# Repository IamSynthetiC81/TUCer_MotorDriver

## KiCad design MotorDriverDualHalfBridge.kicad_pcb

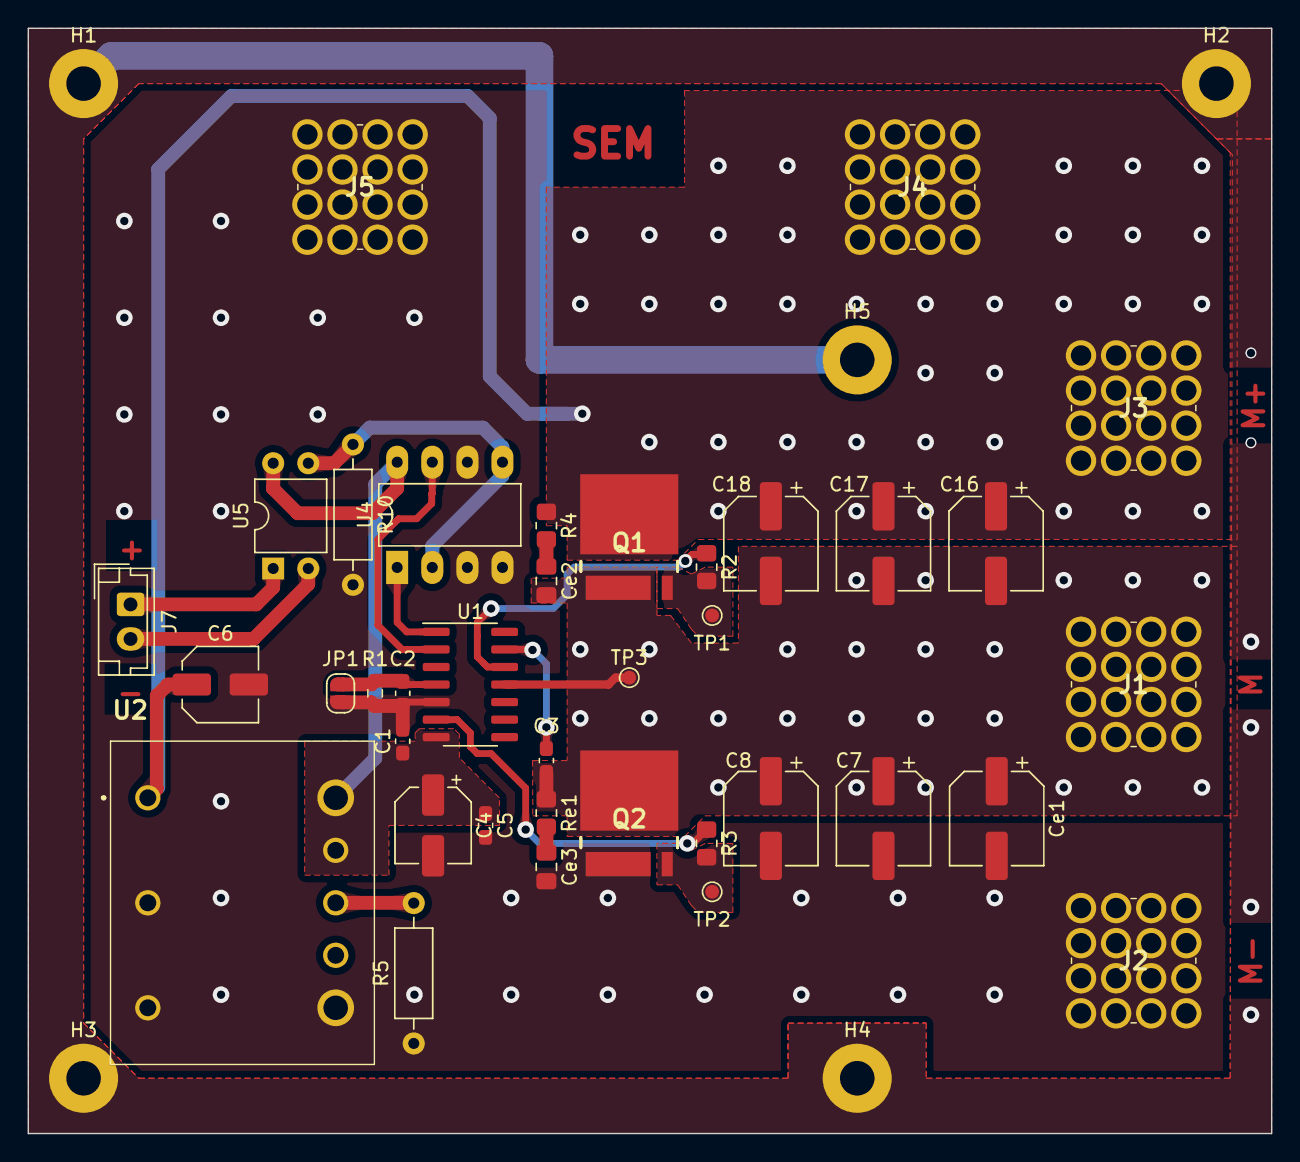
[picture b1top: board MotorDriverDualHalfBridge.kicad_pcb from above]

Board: 2 copper layers, 90.0 x 80.0 mm, 42 parts (0 on the bottom side), 19 nets.

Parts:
C1: 1uF; C_0603_1608Metric_Pad1.08x0.95mm_HandSolder
C2: 1nF; C_0603_1608Metric_Pad1.08x0.95mm_HandSolder
C3: 4.7uF; C_0603_1608Metric_Pad1.08x0.95mm_HandSolder
C4: 22uF; CP_Elec_5x5.8
C5: 0.1uF; C_0603_1608Metric_Pad1.08x0.95mm_HandSolder
C6: 100uF; C_Elec_5x5.8
C7, C8, C16, C17, C18: 100nF; CP_Elec_6.3x5.4_Nichicon
Ce1: 100nF; CP_Elec_6.3x5.4_Nichicon
Ce2: C_{SNUBH}; C_0805_2012Metric_Pad1.18x1.45mm_HandSolder
Ce3: C_{SNUBL}; C_0805_2012Metric_Pad1.18x1.45mm_HandSolder
H1, H2, H3, H4, H5: MountingHole_Pad; MountingHole_2.5mm_Pad
J1: Motor Middle Connection; M5 Screw Terminal
J2: Motor Bottom Connection; M5 Screw Terminal
J3: Motor Upper Connection; M5 Screw Terminal
J4: Batt+; M5 Screw Terminal
J5: Batt-; M5 Screw Terminal
J7: Conn_01x02; JST_EH_B2B-EH-A_1x02_P2.50mm_Vertical
JP1: J_{DT}; SolderJumper-2_P1.3mm_Open_RoundedPad1.0x1.5mm
Q1, Q2: IAUA250N04S6N005; IAUA250N04S6N005AUMA1
R1: R_{DT}; R_0603_1608Metric_Pad0.98x0.95mm_HandSolder
R2: R_{G}_{H}; R_0805_2012Metric_Pad1.20x1.40mm_HandSolder
R3: R_{G}_{L}; R_0805_2012Metric_Pad1.20x1.40mm_HandSolder
R4: R_{SNUBH}; R_0805_2012Metric_Pad1.20x1.40mm_HandSolder
R5: 1.8k; R_Axial_DIN0207_L6.3mm_D2.5mm_P10.16mm_Horizontal
R10: R_{DT}; R_Axial_DIN0207_L6.3mm_D2.5mm_P10.16mm_Horizontal
Re1: R_{SNUBL}; R_0805_2012Metric_Pad1.20x1.40mm_HandSolder
TP1: V_{Gate_HI}; TestPoint_Pad_D1.0mm
TP2: V_{Gate_LO}; TestPoint_Pad_D1.0mm
TP3: V_{Drain}; TestPoint_Pad_D1.0mm
U1: 2ED21824S06J; SO-14_3.9x8.65mm_P1.27mm
U2: I3A4W005A150V001R
U4: LM358; DIP-8_W7.62mm_LongPads
U5: EL817; DIP-4_W7.62mm

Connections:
+12V: C1.1, C4.1, C5.1, U1.7 (VCC), U2.7 (SENSE), U2.8 (V_{OUT}+), U4.8 (V+), U5.4
+BATT: C6.1, C16.1, C17.1, C18.1, J3.1, J3.2, J3.3, J3.4, J3.5, J3.6 (e), J3.7, J3.8, J3.9, J3.10 (e), J3.11, J3.12, J3.13, J3.14 (e), J3.15 (Pin_1), J3.16 (Pin_1), J4.1, J4.2, J4.3, J4.4, J4.5, J4.6 (e), J4.7, J4.8, J4.9, J4.10 (e), J4.11, J4.12, J4.13, J4.14 (e), J4.15 (Pin_1), J4.16 (Pin_1), Q1.6 (D), R4.1, U2.1 (V_{IN+})
/H_{IN}: U1.1 (HIN), U4.1
/LOAD: C3.2, C7.1, C8.1, C16.2, C17.2, C18.2, Ce1.1, Ce2.2, J1.1, J1.2, J1.3, J1.4, J1.5, J1.6 (e), J1.7, J1.8, J1.9, J1.10 (e), J1.11, J1.12, J1.13, J1.14 (e), J1.15 (Pin_1), J1.16 (Pin_1), Q1.1 (S), Q2.6 (D), Re1.1, TP3.1, U1.11 (V_{S})
/L_{IN}: U1.2 (LIN), U4.7
/MotorDrive +: J7.1, U5.1
/MotorDriver -: J7.2, U5.2
/V_{GH}: Q1.5 (G), R2.2, TP1.1
/V_{GL}: Q2.5 (G), R3.2, TP2.1
Earth_Clean: H1.1, H2.1, H3.1, H4.1, H5.1
GNDPWR: C1.2, C2.2, C4.2, C5.2, C6.2, C7.2, C8.2, Ce1.2, Ce3.2, J2.1, J2.2, J2.3, J2.4, J2.5, J2.6 (e), J2.7, J2.8, J2.9, J2.10 (e), J2.11, J2.12, J2.13, J2.14 (e), J2.15 (Pin_1), J2.16 (Pin_1), J5.1, J5.2, J5.3, J5.4, J5.5, J5.6 (e), J5.7, J5.8, J5.9, J5.10 (e), J5.11, J5.12, J5.13, J5.14 (e), J5.15 (Pin_1), J5.16 (Pin_1), JP1.1 (A), Q2.1 (S), R1.2, R5.1, R10.2, U1.5 (COM), U2.2 (ON/OFF), U2.3 (V_{IN-}), U2.4 (V_{OUT}-), U4.3 (+), U4.4 (V-), U4.6 (-)
unnamed: Ce2.1, R4.2
unnamed: Ce3.1, Re1.2
unnamed: C2.1, JP1.2 (B), R1.1, U1.4 (DT)
unnamed: R2.1, U1.12 (HO)
unnamed: R3.1, U1.6 (LO)
unnamed: C3.1, U1.13 (V_{B})
unnamed: R5.2, U2.6 (TRIM)
unnamed: R10.1, U4.2 (-), U4.5 (+), U5.3

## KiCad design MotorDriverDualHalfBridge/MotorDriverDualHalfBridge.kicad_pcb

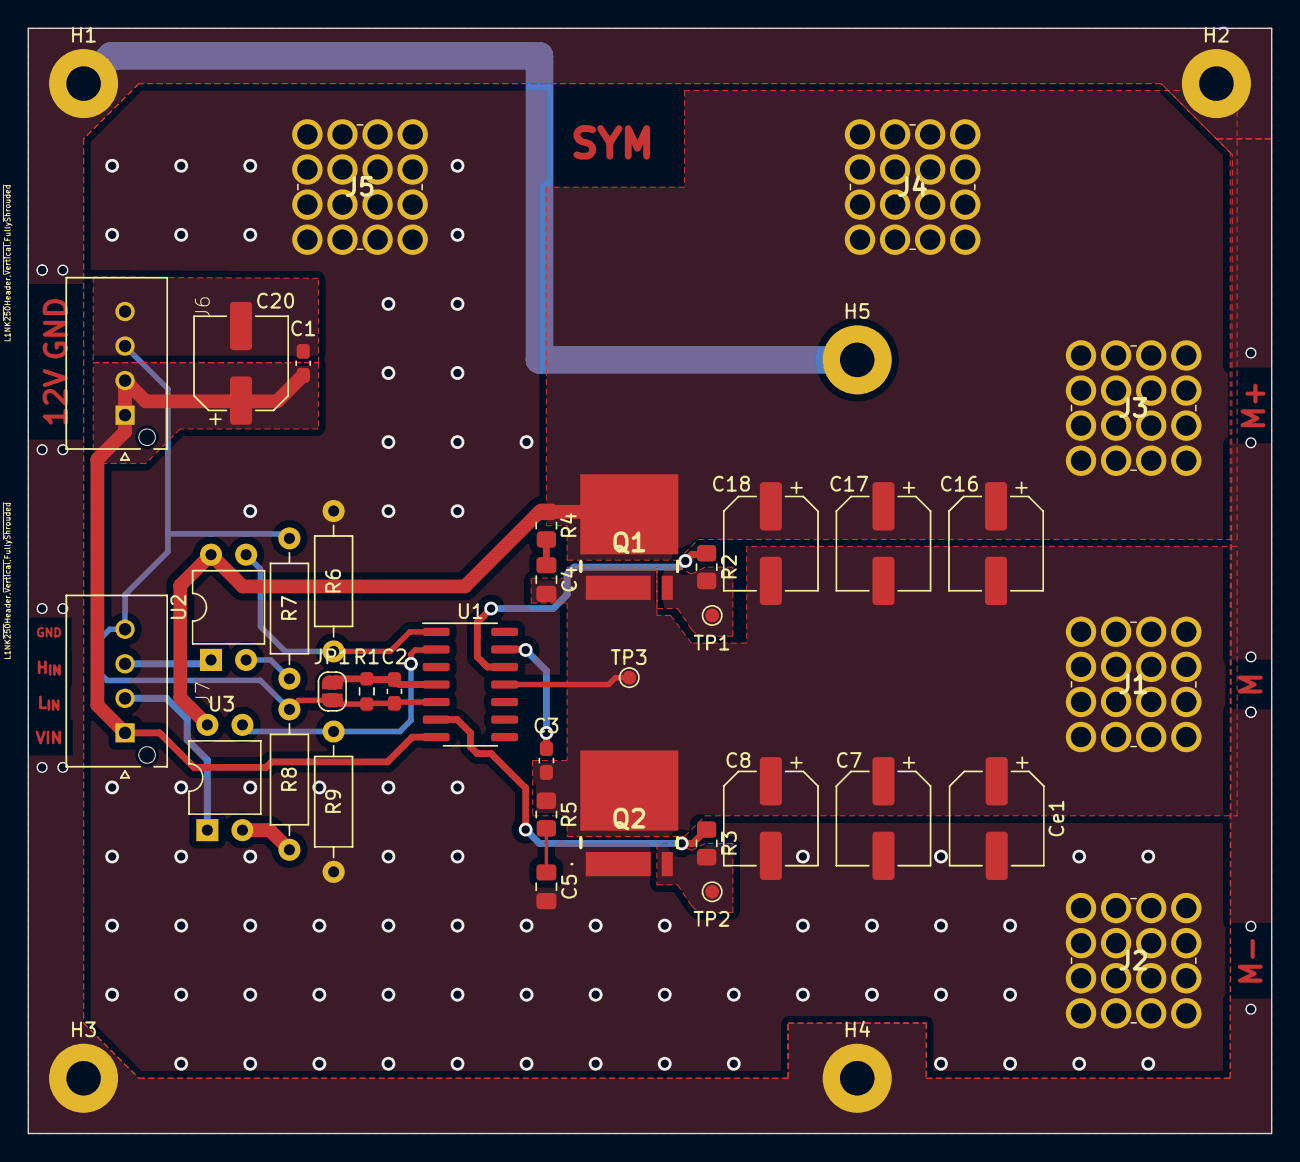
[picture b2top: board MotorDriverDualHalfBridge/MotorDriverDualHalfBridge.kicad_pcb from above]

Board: 2 copper layers, 90.0 x 80.0 mm, 42 parts (0 on the bottom side), 20 nets.

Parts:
C1: 1uF; C_0603_1608Metric_Pad1.08x0.95mm_HandSolder
C2: 1nF; C_0603_1608Metric_Pad1.08x0.95mm_HandSolder
C3: 4.7uF; C_0603_1608Metric_Pad1.08x0.95mm_HandSolder
C4: C_{SNUBH}; C_0805_2012Metric_Pad1.18x1.45mm_HandSolder
C5: C_{SNUBL}; C_0805_2012Metric_Pad1.18x1.45mm_HandSolder
C7, C8, C16, C17, C18: 100nF; CP_Elec_6.3x5.4_Nichicon
C20: 100uF; CP_Elec_6.3x5.4_Nichicon
Ce1: 100nF; CP_Elec_6.3x5.4_Nichicon
H1, H2, H3, H4, H5: MountingHole_Pad; MountingHole_2.5mm_Pad
J1: Motor Middle Connection; M5 Screw Terminal
J2: Motor Bottom Connection; M5 Screw Terminal
J3: Motor Upper Connection; M5 Screw Terminal
J4: Batt+; M5 Screw Terminal
J5: Batt-; M5 Screw Terminal
J6, J7: Conn_01x04; MOLEX_2078430004_L1NK_250_4-PIN
JP1: J_{DT}; SolderJumper-2_P1.3mm_Open_RoundedPad1.0x1.5mm
Q1, Q2: IAUA250N04S6N005; IAUA250N04S6N005AUMA1
R1: R_{DT}; R_0603_1608Metric_Pad0.98x0.95mm_HandSolder
R2: R_{G}_{H}; R_0805_2012Metric_Pad1.20x1.40mm_HandSolder
R3: R_{G}_{L}; R_0805_2012Metric_Pad1.20x1.40mm_HandSolder
R4: R_{SNUBH}; R_0805_2012Metric_Pad1.20x1.40mm_HandSolder
R5: R_{SNUBL}; R_0805_2012Metric_Pad1.20x1.40mm_HandSolder
R6, R7, R8, R9: R_{DT}; R_Axial_DIN0207_L6.3mm_D2.5mm_P10.16mm_Horizontal
TP1: V_{Gate_HI}; TestPoint_Pad_D1.0mm
TP2: V_{Gate_LO}; TestPoint_Pad_D1.0mm
TP3: V_{Drain}; TestPoint_Pad_D1.0mm
U1: 2ED21824S06J; SO-14_3.9x8.65mm_P1.27mm
U2, U3: EL817; DIP-4_W7.62mm

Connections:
+12V: C1.1, C20.1, J6.1, J6.2, J7.1, U1.7 (VCC)
+BATT: C16.1, C17.1, C18.1, J3.1, J3.2, J3.3, J3.4, J3.5, J3.6 (e), J3.7, J3.8, J3.9, J3.10 (e), J3.11, J3.12, J3.13, J3.14 (e), J3.15 (Pin_1), J3.16 (Pin_1), J4.1, J4.2, J4.3, J4.4, J4.5, J4.6 (e), J4.7, J4.8, J4.9, J4.10 (e), J4.11, J4.12, J4.13, J4.14 (e), J4.15 (Pin_1), J4.16 (Pin_1), Q1.6 (D), R4.1, U2.4, U3.4
/LOAD: C3.2, C4.2, C7.1, C8.1, C16.2, C17.2, C18.2, Ce1.1, J1.1, J1.2, J1.3, J1.4, J1.5, J1.6 (e), J1.7, J1.8, J1.9, J1.10 (e), J1.11, J1.12, J1.13, J1.14 (e), J1.15 (Pin_1), J1.16 (Pin_1), Q1.1 (S), Q2.6 (D), R5.1, TP3.1, U1.11 (V_{S})
/V_{GH}: Q1.5 (G), R2.2, TP1.1
/V_{GL}: Q2.5 (G), R3.2, TP2.1
Earth_Clean: H1.1, H2.1, H3.1, H4.1, H5.1
GND: C1.2, C2.2, C20.2, J6.3, J6.4, J7.4, JP1.1 (A), R1.2, R7.2, R8.2, U1.5 (COM)
GNDPWR: C5.2, C7.2, C8.2, Ce1.2, J2.1, J2.2, J2.3, J2.4, J2.5, J2.6 (e), J2.7, J2.8, J2.9, J2.10 (e), J2.11, J2.12, J2.13, J2.14 (e), J2.15 (Pin_1), J2.16 (Pin_1), J5.1, J5.2, J5.3, J5.4, J5.5, J5.6 (e), J5.7, J5.8, J5.9, J5.10 (e), J5.11, J5.12, J5.13, J5.14 (e), J5.15 (Pin_1), J5.16 (Pin_1), Q2.1 (S), R6.2, R9.2
H_{IN}: J7.3, U2.1
H_{IN}_{_ISO}: R6.1, U1.1 (HIN), U2.3
L_{IN}: J7.2, U3.1
L_{IN}_{_ISO}: R9.1, U1.2 (LIN), U3.3
unnamed: C4.1, R4.2
unnamed: C5.1, R5.2
unnamed: C2.1, JP1.2 (B), R1.1, U1.4 (DT)
unnamed: R7.1, U2.2
unnamed: R8.1, U3.2
unnamed: R2.1, U1.12 (HO)
unnamed: R3.1, U1.6 (LO)
unnamed: C3.1, U1.13 (V_{B})

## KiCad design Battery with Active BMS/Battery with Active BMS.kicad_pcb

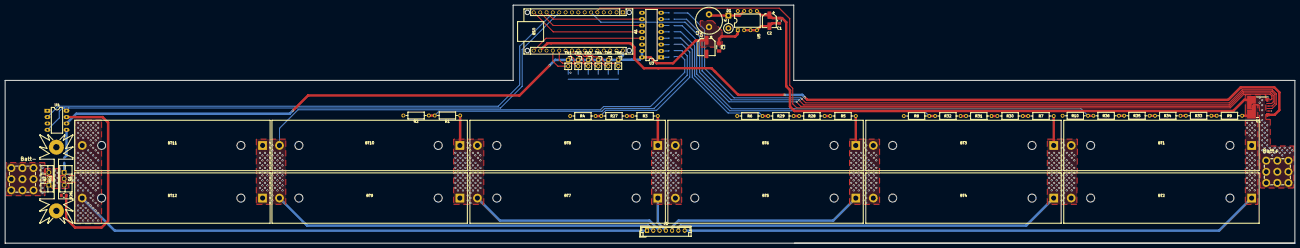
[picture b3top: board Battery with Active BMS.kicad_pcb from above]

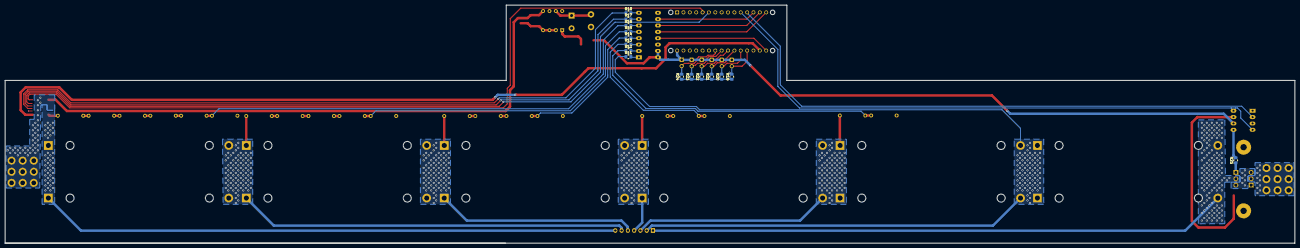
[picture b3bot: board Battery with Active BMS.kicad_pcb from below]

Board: 2 copper layers, 514.8 x 95.0 mm, 71 parts (15 on the bottom side), 56 nets.

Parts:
A1: Arduino_Nano_v2.x; Arduino_Nano_WithMountingHoles
BT1, BT2, BT3, BT4, BT5, BT6, BT7, BT8, BT9, BT10, BT11, BT12: Battery_Cell; BatteryHolder_MPD_BH-18650-PC2
C1: 100nF; C_0805_2012Metric_Pad1.18x1.45mm_HandSolder
C2: 22uF; CP_Elec_5x5.8
C3: 10n; C_1206_3216Metric_Pad1.33x1.80mm_HandSolder
C4: 220uF; CP_Elec_6.3x5.8
D1: 1N5817; D_DO-15_P5.08mm_Vertical_KathodeUp
HS1: Heatsink_Pad_2Pin; Heatsink_Fischer_SK104-STC-STIC_35x13mm_2xDrill2.5mm
J1: Balancer Connector; JST_EH_B7B-EH-A_1x07_P2.50mm_Vertical
J2, J3: 74651195R; Wuerth_REDCUBE-THR_WP-THRSH_74651195_THR
L1: 100uH; L_Radial_D10.5mm_P5.00mm_Abacron_AISR-01
Q1, Q2: IPP015N04NGXKSA1; TO-220F-3_Vertical
R1, R2, R3, R4, R5, R6, R7, R8, R9, R10, R27, R28, R29, R30, R31, R32, R33, R34, R35, R36: 1M; R_Axial_DIN0207_L6.3mm_D2.5mm_P10.16mm_Horizontal
R11, R12, R13, R14, R15, R16, R17, R18: 220; R_0805_2012Metric_Pad1.20x1.40mm_HandSolder
R19, R20, R21, R22, R23, R24: 100k; R_0805_2012Metric_Pad1.20x1.40mm_HandSolder
R25, R26: 3.3Ω; R_0805_2012Metric_Pad1.20x1.40mm_HandSolder
TH1, TH2, TH3, TH4, TH5, TH6: 100k; PinSocket_1x02_P2.54mm_Vertical
U1: TLI4971A050T5UE0001XUMA1; Infineon_PG-TISON-8-5
U3: MCP3008; DIP-16_W7.62mm_LongPads
U4: TC4427CPA; DIP-8_W7.62mm_LongPads
U5: LM2574HVN-5; DIP-8_W7.62mm

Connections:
+3.3V: A1.17 (3V3), U1.1 (VDD)
+5V: A1.30 (VIN), C3.1, C4.1, L1.2, TH1.1, TH2.1, TH3.1, TH4.1, TH5.1, TH6.1, U3.15 (Vref), U3.16 (Vdd), U4.6 (VDD), U5.1 (FB)
+BATT: C1.1, C2.1, J2.1, U1.7 (IP-), U5.5 (VIN)
-BATT: A1.4 (GND), A1.29 (GND), BT11.2 (-), BT12.2 (-), C1.2, C2.2, C3.2, C4.2, D1.2 (A), J1.1, Q1.2 (D), R2.2, R4.2, R6.2, R8.2, R10.2, R19.1, R20.1, R21.1, R22.1, R23.1, R24.1, U1.2 (GND), U3.9 (DGND), U3.14 (AGND), U4.3 (GND), U5.2 (SGND), U5.3 (~ON/OFF), U5.4 (PGND)
/A_{AOUT}: R17.1, U1.4 (AOUT)
/CLK: A1.16 (D13), U3.13 (CLK)
/Cell1: BT9.2 (-), BT10.2 (-), BT11.1 (+), BT12.1 (+), J1.2, R11.1
/Cell2: R1.2, R2.1, R12.1
/Cell3: R4.1, R13.1, R27.2
/Cell4: R6.1, R14.1, R29.2
/Cell5: R8.1, R15.1, R32.2
/Cell6: R10.1, R16.1, R36.2
/D_{IN}: A1.14 (D11), U3.11 (Din)
/D_{OUT}: A1.15 (D12), U3.12 (Dout)
/M1: A1.11 (D8), U4.4 (IN_B)
/M2: A1.12 (D9), U4.2 (IN_A)
/OCD1: A1.6 (D3), U1.5 (OCD1)
/OCD2: A1.5 (D2), U1.6 (OCD2)
/V_{REF}: R18.1, U1.3 (VREF)
/~CS: A1.13 (D10), U3.10 (~CS/SHDN)
GND: J3.1, Q2.2 (D)
unnamed: A1.19 (A0), R19.2, TH1.2
unnamed: A1.20 (A1), R20.2, TH2.2
unnamed: A1.21 (A2), R21.2, TH3.2
unnamed: A1.22 (A3), R22.2, TH4.2
unnamed: A1.23 (A4), R23.2, TH5.2
unnamed: A1.24 (A5), R24.2, TH6.2
unnamed: BT1.1 (+), BT2.1 (+), J1.7, R9.1, U1.8 (IP+)
unnamed: BT1.2 (-), BT2.2 (-), BT3.1 (+), BT4.1 (+), J1.6, R7.1
unnamed: BT3.2 (-), BT4.2 (-), BT5.1 (+), BT6.1 (+), J1.5, R5.1
unnamed: BT5.2 (-), BT6.2 (-), BT7.1 (+), BT8.1 (+), J1.4, R3.1
unnamed: BT7.2 (-), BT8.2 (-), BT9.1 (+), BT10.1 (+), J1.3, R1.1
unnamed: D1.1 (K), L1.1, U5.7 (OUT)
unnamed: Q1.1 (G), R25.1
unnamed: Q1.3 (S), Q2.3 (S)
unnamed: Q2.1 (G), R26.1
unnamed: R3.2, R27.1
unnamed: R5.2, R28.1
unnamed: R28.2, R29.1
unnamed: R7.2, R30.1
unnamed: R30.2, R31.1
unnamed: R31.2, R32.1
unnamed: R9.2, R33.1
unnamed: R33.2, R34.1
unnamed: R34.2, R35.1
unnamed: R35.2, R36.1
unnamed: R11.2, U3.1 (CH0)
unnamed: R12.2, U3.2 (CH1)
unnamed: R13.2, U3.3 (CH2)
unnamed: R14.2, U3.4 (CH3)
unnamed: R15.2, U3.5 (CH4)
unnamed: R16.2, U3.6 (CH5)
unnamed: R17.2, U3.7 (CH6)
unnamed: R18.2, U3.8 (CH7)
unnamed: R26.2, U4.7 (~OUT_A)
unnamed: R25.2, U4.5 (~OUT_B)

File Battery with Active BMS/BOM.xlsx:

Ref | Qnty | Value | Name | Footprint | Description | Vendor | Link
C1 | 1 | 100nF | C | Capacitor_SMD:C_0805_2012Metric_Pad1.18x1.45mm_HandSolder | Unpolarized capacitor | ACDC | https://www.acdcshop.gr/capacitorceramicmlcc100nf50vx7r10smd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
C2 | 1 | 22uF | C_Polarized_US | Capacitor_SMD:CP_Elec_5x5.8 | Polarized capacitor, US symbol | ACDC | https://www.acdcshop.gr/capacitorelectrolyticlowimpedancesmd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
C3 | 1 | 10n | C | Capacitor_SMD:C_1206_3216Metric_Pad1.18x1.45mm_HandSolder | Unpolarized capacitor | ACDC | https://www.acdcshop.gr/capacitorceramicmlcc10nf50vx7r10smd1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
C4 | 1 | 220uF | C_Polarized_US | Capacitor_SMD:CP_Elec_6.3x5.8 | Polarized capacitor, US symbol | ACDC | https://www.acdcshop.gr/capacitorelectrolyticlowimpedancesmd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
D1 | 1 | D_Schottky | 1N5817 | Diode_THT:D_DO-15_P5.08mm_Vertical_KathodeUp | Schottky diode | ACDC | https://www.acdcshop.gr/diodeschottkyrectifying20v1ado15-p-2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
HS1, HS2 | 2 | MOS Heatsink | Heatsink_Pad | Heatsink:Heatsink_Fischer_FK224xx2201_25x8.3mm | Heatsink with electrical connection, 2 pin | ACDC | https://www.acdcshop.gr/heatsinkutype21kw635mmblackenedto220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
J1 | 1 | Balancer Connector | Conn_01x07_Socket | Connector_PinSocket_2.54mm:PinSocket_1x07_P2.54mm_Vertical | Connector for charger ONLY FOR PROP. BATTERY | Grobotronix | https://grobotronics.com/jst-xh-conector-7-pin-male-2.5mm.html
J1 | 1 | Balancer Connector | Conn_01x05_Socket | Connector_PinSocket_2.54mm:PinSocket_1x05_P2.54mm_Vertical | Connector for Charger ONLY FOR ICS BATTERY | Grobotronix | https://grobotronics.com/jst-xh-conector-5-pin-male-2.5mm.html
J2, J3 | 2 | 74651195R | 74651195R_1 | TerminalBlock_Wuerth:Wuerth_REDCUBE-THR_WP-THRSH_74651195_THR | Screw Terminal | Mouser | Υπάρχει ήδη παραγγελία
L1 | 1 | 100uH | L | Inductor_THT:L_Radial_D10.5mm_P5.00mm_Abacron_AISR-01 | Inductor | Grobotronix | https://grobotronics.com/wire-inductor-100uh-el.html
Q1, Q2 | 2 | IPP015N04NGXKSA1 | Q_NMOS_GDS | Package_TO_SOT_THT:TO-220-3_Vertical | N-MOSFET | ACDC | https://www.acdcshop.gr/transistornmosfetunipolar40v120a250w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
R1, R2, R3, R4, R5, R6, R7, R8, R9, R10, R27, R28, R29, R30, R31, R32, R33, R34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 | 20 | 1M | R | Resistor_THT:R_Axial_DIN0207_L6.3mm_D2.5mm_P10.16mm_Horizontal | Resistor | ACDC | https://www.acdcshop.gr/resistormetalfilmtht1m04w0121625x63m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
R11, R12, R13, R14, R15, R16, R17, R18 | 8 | 220Ω | R | Resistor_SMD:R_0805_2012Metric_Pad1.20x1.40mm_HandSolder | Resistor | ACDC | https://www.acdcshop.gr/resistorthickfilmsmd08052200125w1552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
R19, R20, R21, R22, R23, R24 | 6 | 100k | R | Resistor_SMD:R_0805_2012Metric_Pad1.20x1.40mm_HandSolder | Resistor | ACDC | https://www.acdcshop.gr/resistorthickfilmsmd0805100k125mw155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
R25, R26 | 2 | 3.3Ω | R | Resistor_SMD:R_0805_2012Metric_Pad1.20x1.40mm_HandSolder | Resistor | ACDC | https://www.acdcshop.gr/resistorthickfilmsmd080533omega125mw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
TH1, TH2, TH3, TH4, TH5, TH6 | 6 | 100k | Thermistor_NTC | Connector_PinSocket_2.54mm:PinSocket_1x02_P2.54mm_Vertical | Temperature dependent resistor, negative temperature coefficient | Grobotronix | https://grobotronics.com/thermistor-100kohm-with-cable-for-3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
U1 | 1 | TLI4971A050T5UE0001XUMA1 | TLI4971A050T5UE0001XUMA1 | Package_SON:Infineon_PG-TISON-8-5 | Current Sensor | Mouser | Υπάρχει ήδη παραγγελία
U3 | 1 | MCP3008 | MCP3008 | Package_DIP:DIP-16_W7.62mm_LongPads | A/D Converter, 10-Bit, 8-Channel, SPI Interface , 2.7V-5.5V | Grobotronix | https://grobotronics.com/mcp3008-10bit-8-channel-adc-spi.html
U4 | 1 | TC4427CPA | TC4427CPA | Package_DIP:DIP-8_W7.62mm_LongPads | Mosfet Driver | ACDC | https://www.acdcshop.gr/driver15achannels2invertnoninvert452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
U5 | 1 | LM2574HVN-5 | LM2574HVN-5 | Package_DIP:DIP-8_W7.62mm | DC/DC Power Supply | Grobotronix | https://grobotronics.com/dc-dc-converter-step-down-40v-5v-0.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

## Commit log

2023-03-04 u[date
2023-03-07 Added Excel file
2023-03-08 Schem V2
2023-03-10 PCB V0.1
2023-03-12 Updated Sims
2023-03-17 Updated Simulations
2023-03-17 Updated Schematic
2023-03-23 Added Parent
2023-03-25 Worked on Parent - Move Workspace to cloud
2023-03-27 Updated Parent further - Move workspace to cloud
2023-03-29 Added BOM
2023-03-31 Updated Parent - Moved workspace to cloud
2023-04-04 Added Active BMS Schem - Moved Workspace to cloud
2023-04-06 Updated Active BMS and BOM
2023-04-07 Updated Battery with Active BMS Schem&PCB&BOM
2023-05-02 Updated Motor Driver Dual Half Bridge
2023-05-02 Motor Driver V1.0
2023-05-03 Fixed traces under connectors
2023-05-10 Motor Driver V1.1
2023-05-16 Motor Driver V1.01
2023-05-18 Added PDFs
